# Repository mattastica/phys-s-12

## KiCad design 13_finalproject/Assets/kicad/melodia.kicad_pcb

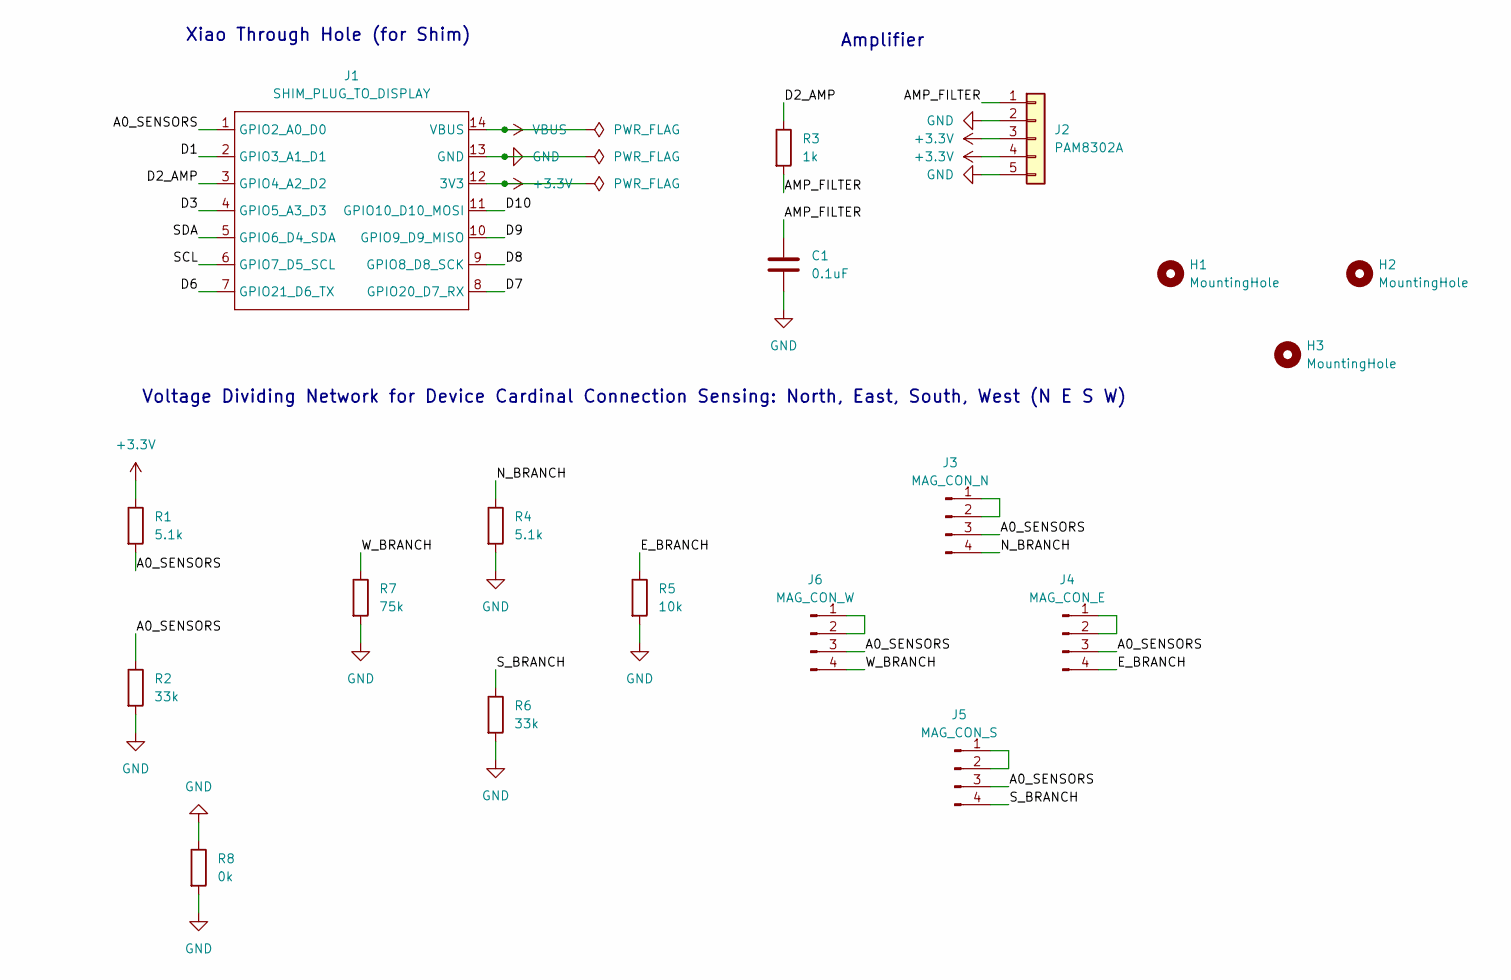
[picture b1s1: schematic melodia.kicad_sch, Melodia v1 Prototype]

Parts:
C1: 0.1uF; C_Disc_D5.0mm_W2.5mm_P5.00mm
H1, H2, H3: MountingHole; MountingHole_3.7mm
J1: SHIM_PLUG_TO_DISPLAY; XIAO-ESP32-C3-DIP
J2: PAM8302A; PinHeader_1x05_P2.54mm_Vertical
J3: MAG_CON_N; PinHeader_1x04_P2.54mm_Vertical
J4: MAG_CON_E; PinHeader_1x04_P2.54mm_Vertical
J5: MAG_CON_S; PinHeader_1x04_P2.54mm_Vertical
J6: MAG_CON_W; PinHeader_1x04_P2.54mm_Vertical
R1, R4: 5.1k; R_1206_3216Metric_Pad1.30x1.75mm_HandSolder
R2, R6: 33k; R_1206_3216Metric_Pad1.30x1.75mm_HandSolder
R3: 1k; R_1206_3216Metric_Pad1.30x1.75mm_HandSolder
R5: 10k; R_1206_3216Metric_Pad1.30x1.75mm_HandSolder
R7: 75k; R_1206_3216Metric_Pad1.30x1.75mm_HandSolder
R8: 0k; R_1206_3216Metric_Pad1.30x1.75mm_HandSolder

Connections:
+3.3V: J1.12 (3V3), J2.3, J2.4, R1.1
/A0_SENSORS: J1.1 (GPIO2_A0_D0), J3.3, J4.3, J5.3, J6.3, R1.2, R2.1
/AMP_FILTER: C1.1, J2.1, R3.2
/D1: J1.2 (GPIO3_A1_D1)
/D2_AMP: J1.3 (GPIO4_A2_D2), R3.1
/D3: J1.4 (GPIO5_A3_D3)
/D6: J1.7 (GPIO21_D6_TX)
/D7: J1.8 (GPIO20_D7_RX)
/D8: J1.9 (GPIO8_D8_SCK)
/D9: J1.10 (GPIO9_D9_MISO)
/D10: J1.11 (GPIO10_D10_MOSI)
/E_BRANCH: J4.4, R5.1
/N_BRANCH: J3.4, R4.1
/SCL: J1.6 (GPIO7_D5_SCL)
/SDA: J1.5 (GPIO6_D4_SDA)
/S_BRANCH: J5.4, R6.1
/W_BRANCH: J6.4, R7.1
GND: C1.2, J1.13 (GND), J2.2, J2.5, R2.2, R4.2, R5.2, R6.2, R7.2, R8.1, R8.2
unnamed: J3.1, J3.2
unnamed: J4.1, J4.2
unnamed: J5.1, J5.2
unnamed: J6.1, J6.2
VBUS: J1.14 (VBUS)

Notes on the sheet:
Voltage Dividing Network for Device Cardinal Connection Sensing: North, East, South, West (N E S W)
Xiao Through Hole (for Shim)
Amplifier

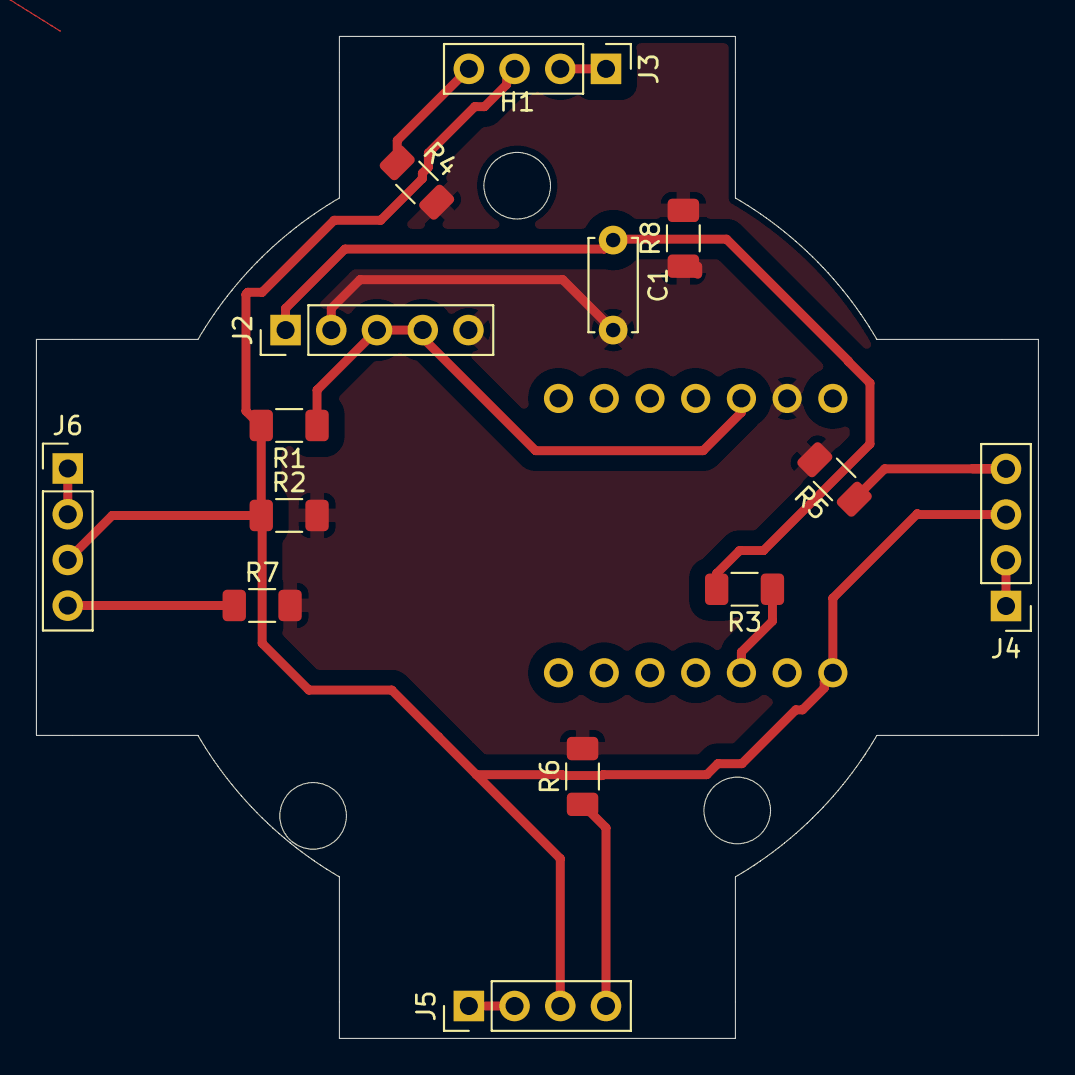
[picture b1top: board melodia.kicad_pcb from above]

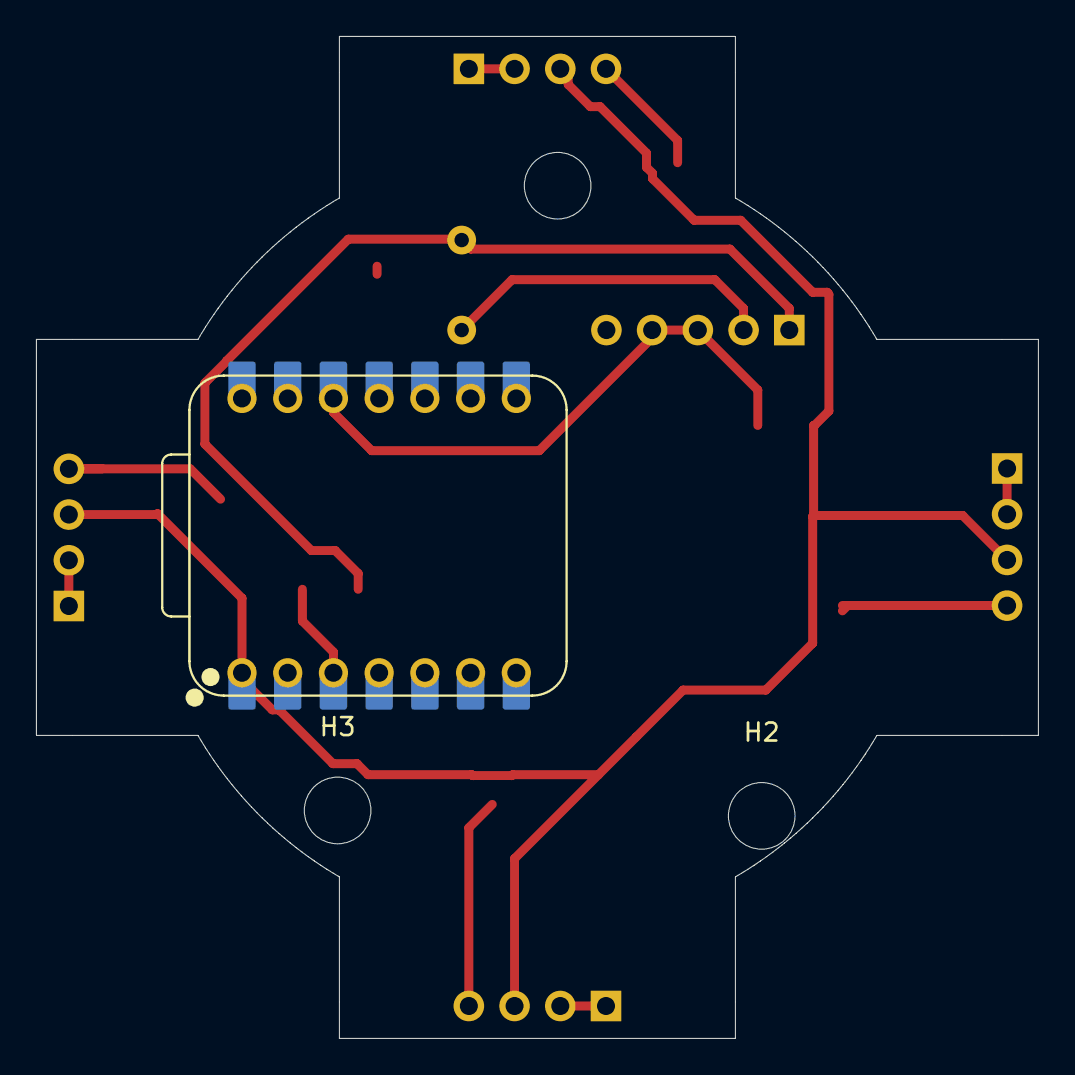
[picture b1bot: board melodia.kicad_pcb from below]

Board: 2 copper layers, 55.7 x 55.7 mm, 18 parts (3 on the bottom side), 13 nets.

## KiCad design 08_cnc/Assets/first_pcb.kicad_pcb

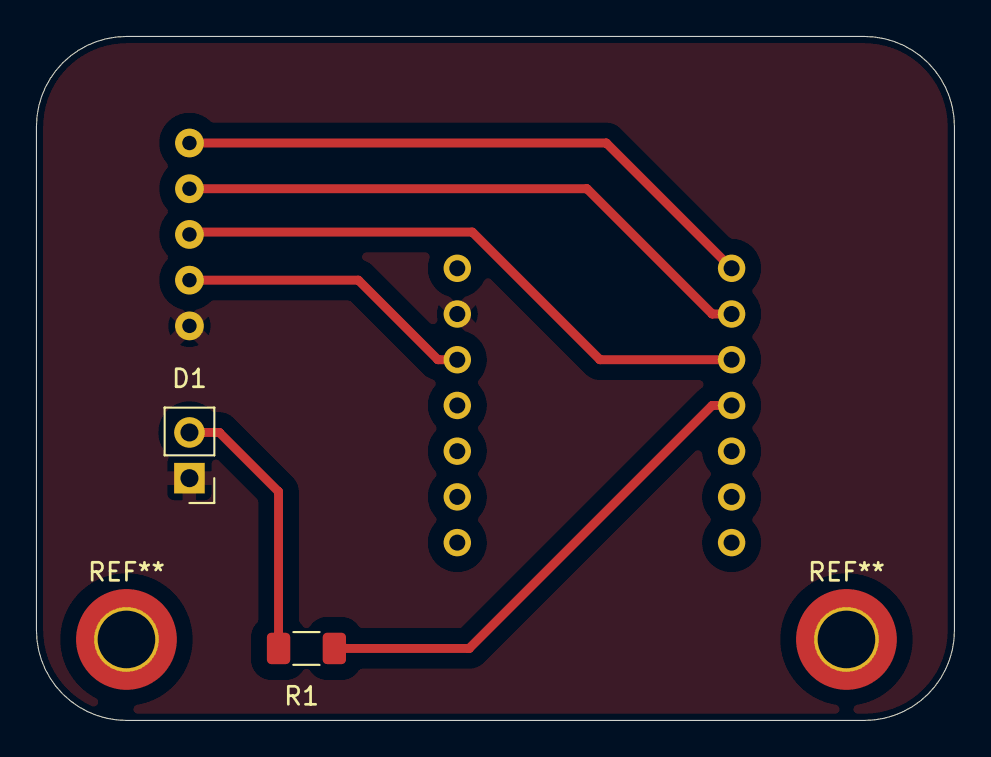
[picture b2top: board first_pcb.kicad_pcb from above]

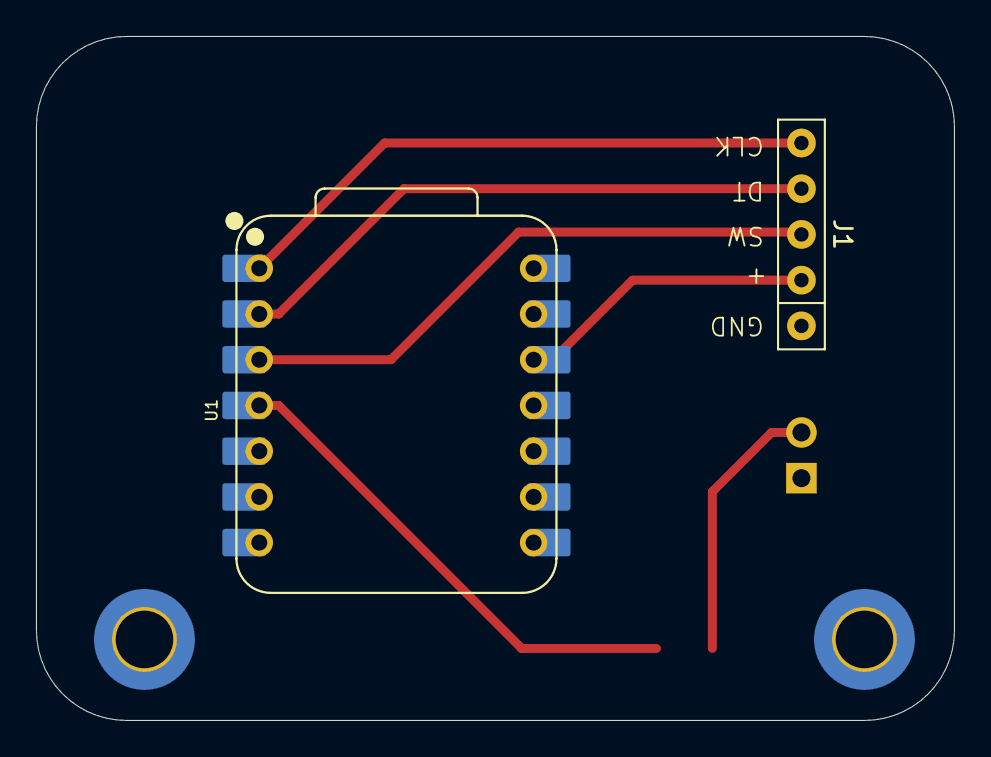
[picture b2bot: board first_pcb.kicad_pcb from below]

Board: 2 copper layers, 51.0 x 38.0 mm, 4 parts (2 on the bottom side), 7 nets.

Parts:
D1: LED; PinHeader_1x02_P2.54mm_Vertical
J1: Conn_01x05_Pin; Rotary_Encoder
R1: 1k; R_1206_3216Metric_Pad1.30x1.75mm_HandSolder
U1: XIAO-ESP32-C3-DIP

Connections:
+3V3: J1.2, U1.12 (3V3)
GND: D1.1 (K), J1.1, U1.13 (GND)
unnamed: D1.2 (A), R1.1
unnamed: J1.3, U1.3 (GPIO4_A2_D2)
unnamed: J1.4, U1.2 (GPIO3_A1_D1)
unnamed: J1.5, U1.1 (GPIO2_A0_D0)
unnamed: R1.2, U1.4 (GPIO5_A3_D3)

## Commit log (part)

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2026-06-23 init commit of template
2026-06-23 add context, name, and contact info.
2026-06-25 add photo to about page
2026-06-25 projects
2026-06-25 page fix
2026-06-27 new site with retro gaming styles, fixes to semantic structure, custom css for animations.
2026-06-27 fix footer+title. add NES harvard logo. fix verbiage. fix bug in config.
2026-06-30 fix title rendering on mobile previews. support iMessage/WhatsApp snippets
2026-06-30 updated projects for design
